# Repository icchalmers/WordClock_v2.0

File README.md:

# WordClock_v2.0

This is a **work-in-progress** build of a word clock. It was originally my final project as part [Fab Academy 2015](http://www.fabacademy.org/) at [Fab Lab Strathclyde](http://www.strath.ac.uk/fablab/).
You can follow the inital evolution of the clock [on my class website](http://fabacademy.org/archives/2015/eu/students/chalmers.iain/final-project-summary-wordclock20.html). The content is also mirrored to [my GitHub Pages site](http://icchalmers.github.io/final-project-summary-wordclock20.html).

This clock is an evolution of [WordClock_v1.0](https://github.com/icchalmers/WordClock_v1.0).

# Project Parts

## Model
The 'Model' folder contains all the Autodesk Inventor 2015 CAD files for the clock. 

The file `Model/wordClock.ipt` is VERY customisable, but has no mounting holes for electronics or any mechanism to support the LED strips.

The 'Model/SolidifiedClockToMake' folder contains a locked down version of the clock i.e. it uses a grid of 11x11. Some parameters may or may not still be adjustable. It has additional holes added to the middle plate for mounting control electronics and holding the LED strips in place.

The main file for the clock is `wordClock_NonParametric.ipt`. The other .ipt files are the individual pieces and are derived from `wordClock_NonParametric.ipt`. They have been compensated for laser kerf using the "kerf" parameter in the master model.

The file `PartsForExport.dwg` has a layout of each of the individual parts. If you change a parameter in the master model, update the individual parts and then update the .dwg.

The lettering is added in CorelDraw - Inventor is a bit rubbish at handling text. I used a modified version of [Source Sans Pro](https://www.google.com/fonts/specimen/Source+Sans+Pro) i.e. I added little structures to support the internal parts of letters.

## hw
The 'hw' folder has the KiCAD files for the two PCB designs: the main control board and the power distribution boards. The power distribution boards also help hold the LED strips in place.

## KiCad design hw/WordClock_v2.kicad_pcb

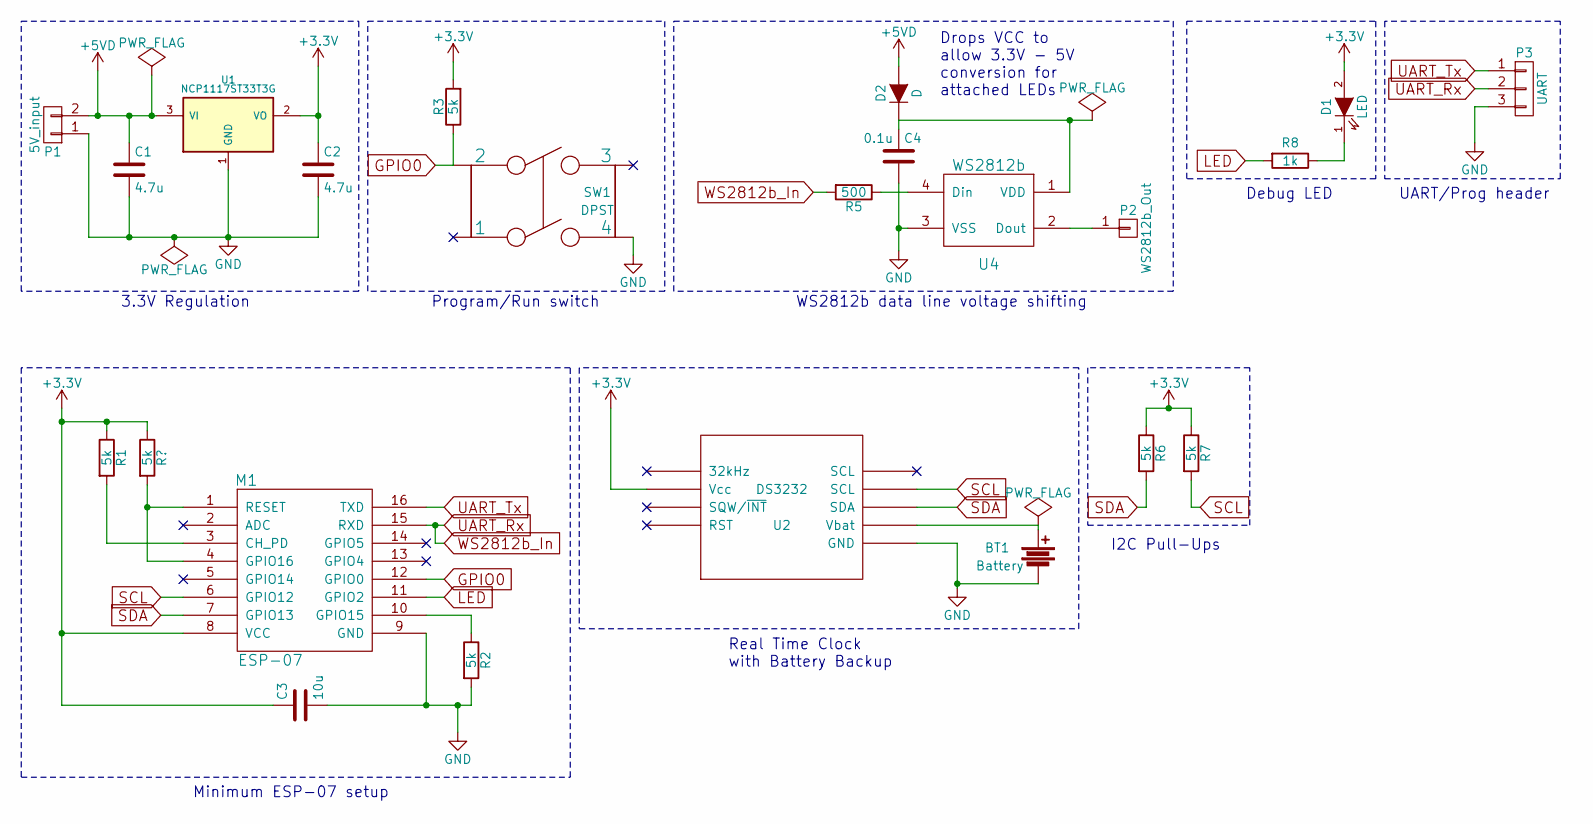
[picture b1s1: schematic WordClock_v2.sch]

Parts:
BT1: Battery; Battery_Holder_Cell_20mm_smd
C1, C2: 4.7u; C_1206_HandSoldering_IainEdit
C3: 10u; C_1206_HandSoldering_IainEdit
C4: 0.1u; C_1206_HandSoldering_IainEdit
D1: LED; C_1206_HandSoldering_IainEdit
D2: D; SOD-123F_HandSolder
M1: ESP-07
P1: 5V_input; Socket_Strip_Straight_1x02
P2: WS2812b_Out; Socket_Strip_Straight_1x01
P3: UART; Socket_Strip_Straight_1x03_IainEdit
R1, R2, R3, R6, R7: 5k; C_1206_HandSoldering_IainEdit
R5: 500; C_1206_HandSoldering_IainEdit
R8: 1k; C_1206_HandSoldering_IainEdit
SW1: DPST; FSM2JSMA_DPST_PushButton
U1: NCP1117ST33T3G; SOT223_HandSolder
U2: DS3232; Maxim_SOIC-20_W20-H2
U4: WS2812b; WS2812b_handsolder

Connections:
+3V3: C2.1, C3.1, D1.2 (A), M1.8 (VCC), R1.1, R3.2, R6.1, R7.1, U1.2 (VO), U2.4 (Vcc); also elsewhere on the board
+5VD: C1.1, D2.2 (A), P1.2, U1.3 (VI)
GND: BT1.2, C1.2, C2.2, C3.2, C4.2, M1.9 (GND), P1.1, P3.3, R2.2, SW1.4, U1.1 (GND), U2.15 (GND), U4.3 (VSS)
GPIO0: M1.12 (GPIO0), R3.1, SW1.2
LED: M1.11 (GPIO2), R8.2
unnamed: BT1.1, U2.16 (Vbat)
unnamed: C4.1, D2.1 (K), U4.1 (VDD)
unnamed: D1.1 (K), R8.1
unnamed 8: M1.1 (RESET), M1.4 (GPIO16); also elsewhere on the board
unnamed: M1.3 (CH_PD), R1.2
unnamed: M1.10 (GPIO15), R2.1
unnamed: P2.1, U4.2 (Dout)
unnamed: R5.1, U4.4 (Din)
SCL: M1.6 (GPIO12), R7.2, U2.18 (SCL)
SDA: M1.7 (GPIO13), R6.2, U2.17 (SDA)
UART_Rx: M1.15 (RXD), P3.2, R5.2
UART_Tx: M1.16 (TXD), P3.1

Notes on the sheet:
3.3V Regulation
WS2812b data line voltage shifting
Real Time Clock with Battery Backup
I2C Pull-Ups
Debug LED
UART/Prog header
Program/Run switch
Minimum ESP-07 setup
Drops VCC to allow 3.3V - 5V conversion for attached LEDs

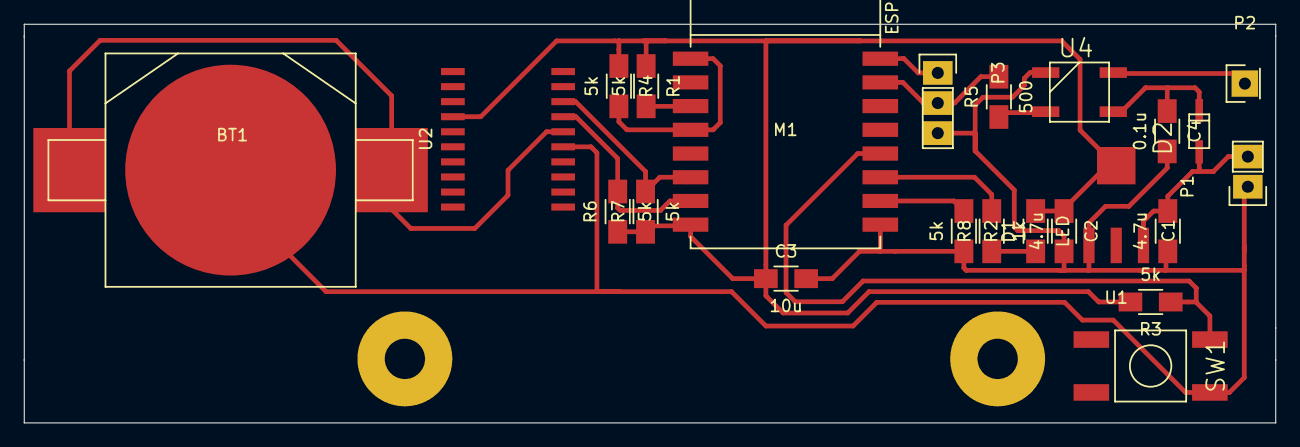
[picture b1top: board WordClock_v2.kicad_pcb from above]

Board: 2 copper layers, 105.5 x 33.6 mm, 23 parts (0 on the bottom side), 17 nets.

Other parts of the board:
R4: 5k; C_1206_HandSoldering_IainEdit

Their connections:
+3V3: R4.1; also elsewhere on the board
unnamed 8: R4.2; also elsewhere on the board

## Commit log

2015-02-10 Added top plate
2015-02-10 Added side plate and set dimensions to match v1.0
2015-02-10 Fixed contraint on top plate stopping being able to increase tabs on front side
2015-02-10 Added mirrors of existing side top and face to make complete box
2015-02-11 Added the middle plate
2015-02-13 Added the construction for the grid
2015-02-13 Added the LED slots
2015-02-13 Added vertical grid divider plus slots
2015-02-13 Added chamfer on vert grid tabs
2015-02-13 Added horizontal slat and slots to join with verticle grid pieces
2015-02-13 Added small chamfer to grid horizontal piece slots. Should help putting together and have minimal light leakage
2015-02-13 Added vent holes and power socket hole to back plate
2015-02-17 Finished wordClock.ipt. Derived wordClock_NonParametric.ipt to add LED supports, as they were going to break most of the parametrics
2015-02-17 Added individual derived part files that are compensated for kerf
2015-02-17 Made all parts cut face be front to make palcement easier
2015-02-17 Fixed missing holes in back and missing grid in front
2015-02-17 Added drawing and pdf of parts ready to take to Inkscape or CorelDRAW for layout and cutting
2015-02-17 Updated files to use 2.5mm thickness for cardboard testing
2015-02-17 Added generated .dwg and .pdf for 2.5mm cardboard
2016-01-19 Initial commit
    updated readme
    Added top plate
    Added side plate and set dimensions to match v1.0
    Fixed contraint on top plate stopping being able to increase tabs on front side
    Added mirrors of existing side top and face to make complete box
    Added the middle plate
2016-01-19 deleting old out-of-date images and cut files, and updating the README
2016-01-19 Adding image of clock to README
2016-06-30 inital commit of sketch, as submitted for FabAcademy
2016-07-08 Getting rid of old Arduino IDE based code. It wasn't even compiling properly in a more recent IDE. The multi-INO file system is pretty terrible. Also library management is basically non-existent. Goi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
2016-07-08 inital commit of blank PlatformIO Eclipse based project
2016-07-08 Adding an example userConfig.h, but making sure the actual file doesnt get added to git as it contains sensitive data e.g. wifi SSID and password
2016-07-08 git subrepo clone git@github.com:Makuna/NeoPixelBus.git sw/WordClock/lib/NeoPixelBus
    subrepo:
    subdir: "sw/WordClock/lib/NeoPixelBus"
    merged: "929d4f7"
    upstream:
    origin: "git@github.com:Makuna/NeoPixelBus.git"
    branch: "master"
2016-07-08 Adding readme about libraries and git subrepos
2016-07-08 Added minimal code to support OTA updates
2016-08-18 Adding basic macros for using the debug LED
2016-08-18 Adding comment header
2016-08-18 Updated PCB to use RDX0/GPIO3 for WS2812b in order to use the NeoEps8266Dma800KbpsMethod of Makuna's NeoPixelBus library
2016-08-18 Added the start of a display driver for controlling all the LEDs on the board
2016-08-18 git subrepo clone https://github.com/tzapu/WiFiManager ./sw/WordClock/lib/WiFiManager
    subrepo:
    subdir: "sw/WordClock/lib/WiFiManager"
    merged: "e0b8acb"
    upstream:
    origin: "https://github.com/tzapu/WiFiManager"
    branch: "master"
2016-08-18 Adding .tavis.yml to gitignore
2016-08-18 Adding WifiManager. The clock can now be configured to connected to different networks without needing to reprogram
2016-08-18 adding includes to main for wifimanager, as suggested in it's example code. It compiles fine in platformio without, but might be necessary if used in the Arduino IDE
2016-08-22 Adding display clear method. Also style cleanup
2016-08-22 Adding an uncrustify config file for use with atom-beautify
2016-08-22 Adding underscore to functions that should not be called externally. Really this should be converted to an OTAManager class. Also adding protoypes for functions to display current OTA status on the d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
2016-08-22 Stle cleanup
2016-08-22 Added OTA status updates to the display
2016-08-22 Forgot to update display on OTA error
2016-08-22 Using colour defined in display instead of hard coded values
2016-08-22 Refactoring file names for WS2812bDisplay class
2016-08-22 Adding TODO to terrible pixel_count variable
2016-08-25 Making colour definitions in the display class be static so can use without creating instance of the class if necessary. Also changed to lower case as upper case was a fallover from when I initially 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
2016-10-24 Adding ability to set groups of pixels (arrays or vectors) to one colour
2016-10-24 Adding pixel mapping for words
2016-10-24 Changing C++ header files to be .hpp extension as that's really what they are, not C header files.
2016-10-24 git subrepo clone https://github.com/PaulStoffregen/Time ./sw/WordClock/lib/Time
    subrepo:
    subdir: "sw/WordClock/lib/Time"
    merged: "22c5947"
    upstream:
    origin: "https://github.com/PaulStoffregen/Time"
    branch: "master"
2017-07-01 Switched to diode-drop method of voltage conversion and changed from switch to push button for entering programming mode
2017-07-01 fixed clearnace issue for making on the denford
2017-07-01 adding files for use on the Denford PCB engraver
2017-07-01 adding power flag annotation
2017-07-03 Updated CH_PD and RST on ESP to use their own pullup resistors. Attached GPIO16 to RST to allow wake from deep sleep
2017-07-03 git subrepo clone --force git@github.com:Makuna/NeoPixelBus.git sw/WordClock/lib/NeoPixelBus/
    subrepo:
    subdir: "sw/WordClock/lib/NeoPixelBus"
    merged: "80f0812"
    upstream:
    origin: "git@github.com:Makuna/NeoPixelBus.git"
    branch: "master"
2017-07-03 git subrepo clone --force https://github.com/PaulStoffregen/Time sw/WordClock/lib/Time
    subrepo:
    subdir: "sw/WordClock/lib/Time"
    merged: "01083f8"
    upstream:
    origin: "https://github.com/PaulStoffregen/Time"
    branch: "master"
2017-07-03 git subrepo clone --force https://github.com/tzapu/WiFiManager sw/WordClock/lib/WiFiManager/
    subrepo:
    subdir: "sw/WordClock/lib/WiFiManager"
    merged: "5e92486"
    upstream:
    origin: "https://github.com/tzapu/WiFiManager"
    branch: "master"
2017-07-03 Updating platformio.ini
